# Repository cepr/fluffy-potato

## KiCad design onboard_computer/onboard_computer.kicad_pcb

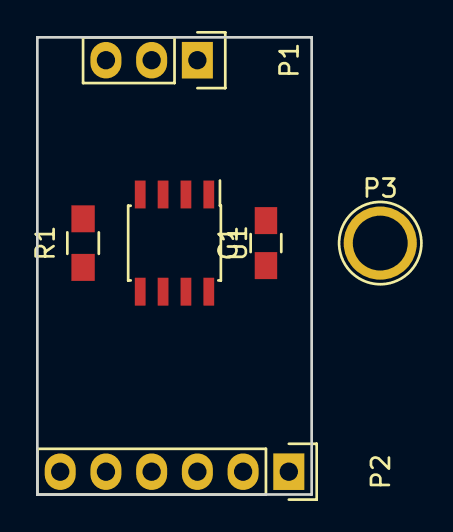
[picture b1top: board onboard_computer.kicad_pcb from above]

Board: 2 copper layers, 15.2 x 25.4 mm, 6 parts (0 on the bottom side), 7 nets, no tracks yet.

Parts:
C1: 220p; C_0805_HandSoldering
P1: CONN_01X03; Pin_Header_Straight_1x03
P2: CONN_01X06; Pin_Header_Straight_1x06
P3: CONN_01X01; 1pin
R1: 4K7; R_0805_HandSoldering
U1: MCP2003B; SOIC-8_3.9x4.9mm_Pitch1.27mm

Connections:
+3V3: P2.5, R1.1
+12V: P2.1, U1.7
GND: C1.2, P2.2, P2.4, P2.6, U1.3, U1.5
unnamed: C1.1, P3.1, U1.6
unnamed: P1.1, U1.2
unnamed: P1.2, R1.2, U1.1
unnamed: P1.3, U1.4
